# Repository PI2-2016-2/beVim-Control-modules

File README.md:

# beVim-Control-modules
Aplicação baixo nível e módulos de controle do projeto BeVim.
#Histórico

. Pedro Henrique Gonçalves Inazawa - Criação

#Introdução

O sistema BeVim se trata de uma bancada de testes, criada com o intuito de fazer ensaios vibracionais em diversas estruturas. Nesse contexto, dentre os 4 grandes módulos do projeto, o sistema de Controle visa fazer uma "ponte' entre as camadas mais inferiores do projeto (sistema mecânico e de rotação do motor) com as camadas de mais alto nível (sistema web), promovendo interação entre ambos. 

Os objetivos desse grande grupo são:

 * promover o controle transparente das funções de vibração da mesa, ao mesmo tempo que fornecendo dados de como ela está operando. 

 * Ser um sistema modular e escalável também, isto é, deve ser possível aumentar a quantidade de sensores e de motores da mesa da forma que melhor convier para os ensaios feitos na mesa.

 * Promover a vibração correta e com uma estimativa de erro, com um melhor ajuste entre as frequencias de 50 a 100 Hz.

##Módulos básicos do sistema de controle

Três sistemas básicos foram criados: 

 * [Sistema de Sensoriamento](Modules/MeasureBoard/Documentation/MeasureBoard.md): Responsável pela leitura e disponibilização dos dados tanto para os módulos de maior nível dentro do sistema (as CPUs, que se comunicam via UART) quanto por ser MESTRE da comunicação i2c com os módulos logo abaixo.

 * [Sistema de Controle de Motores](Modules/MotorControlBoard/Documentation/MotorControlBoard.md): é um módulo controlado por i2c, que se une a rede criada pelo módulo de sensoriamento. Este é capaz de vibrar os motores, informando os dados pela rede para o módulo de sensoriamento.

 * [Subsistema de expansão de Sensores](Modules/ExpansionBoard/Documentation/ExpansionBoard.md): É um módulo que permite expandir a quantidade de sensores no sistema (de 8 em 8 sensores).

Para mais detalhes sobre esse sistema, consulte a [Arquitetura do Sistema](Documentation/SystemArchitecture.md)

Para mais detalhes sobre os protocolos de comunicação implementados pelo projeto, consulte a [Descrição de protocolos](Simulators/BeVim-Protocol-Simulator/Documentation/Protocol.md)

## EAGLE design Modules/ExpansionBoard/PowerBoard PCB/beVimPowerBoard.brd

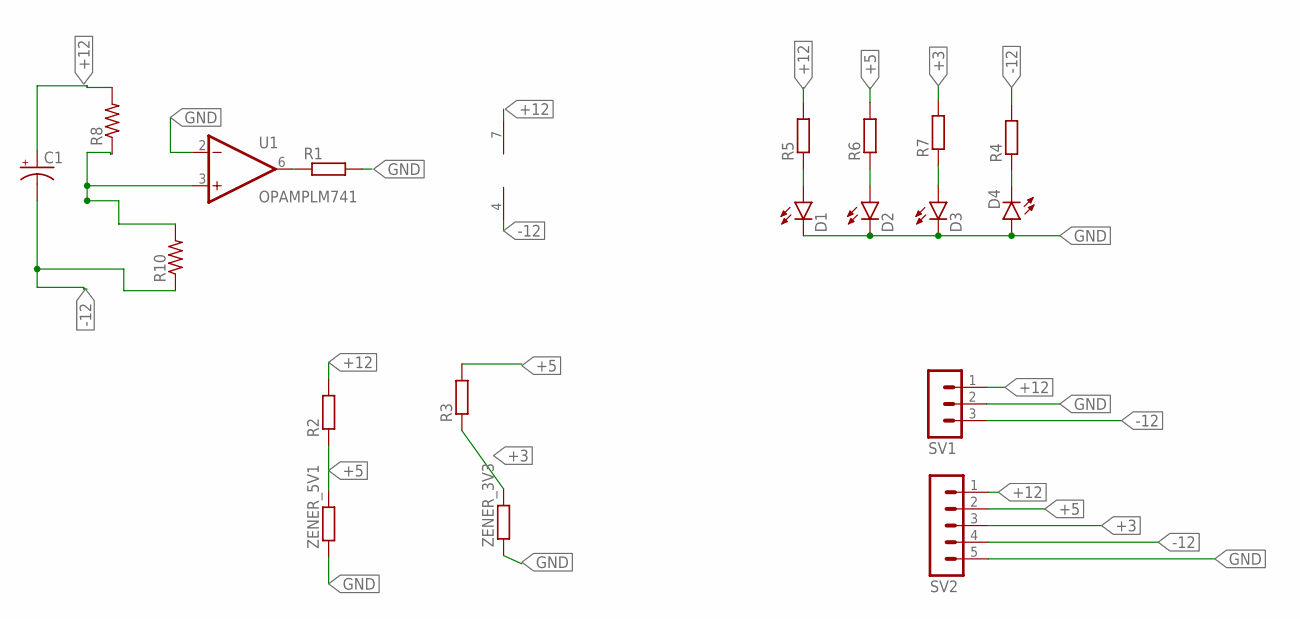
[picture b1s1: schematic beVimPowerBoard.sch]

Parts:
C1: CAPACITOR-POLARIZEDRADIAL-POLARIZED-6.3MM-TANTALUM; RADIAL-POLARIZED-6.3MM-TANTALUM
D1, D2, D3, D4: LED5MM
R1, R2, R3, R4, R5, R6, R7: R-EU_0817/7V; P0817V
R8, R10: R-US_0309/12; 0309/12
SV1: MA03-1
SV2: MA05-1
U1: OPAMPLM741; DIP8
ZENER_3V3, ZENER_5V1: R-EU_0817/7V; P0817V

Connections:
+3: R3.1, R7.2, SV2.3, ZENER_3V3.2
+5: R2.1, R3.2, R6.2, SV2.2, ZENER_5V1.2
+12: C1.+, R2.2, R5.2, R8.2, SV1.1, SV2.1, U1.7 (VCC)
-12: C1.-, R4.2, R10.1, SV1.3, SV2.4, U1.4 (VEE)
GND: D1.K (C), D2.K (C), D3.K (C), D4.A, R1.2, SV1.2, SV2.5, U1.2 (IN-), ZENER_3V3.1, ZENER_5V1.1
unnamed: D1.A, R5.1
unnamed: D2.A, R6.1
unnamed: D3.A, R7.1
unnamed: D4.K (C), R4.1
unnamed: R1.1, U1.6 (OUT)
unnamed: R8.1, R10.2, U1.3 (IN+)

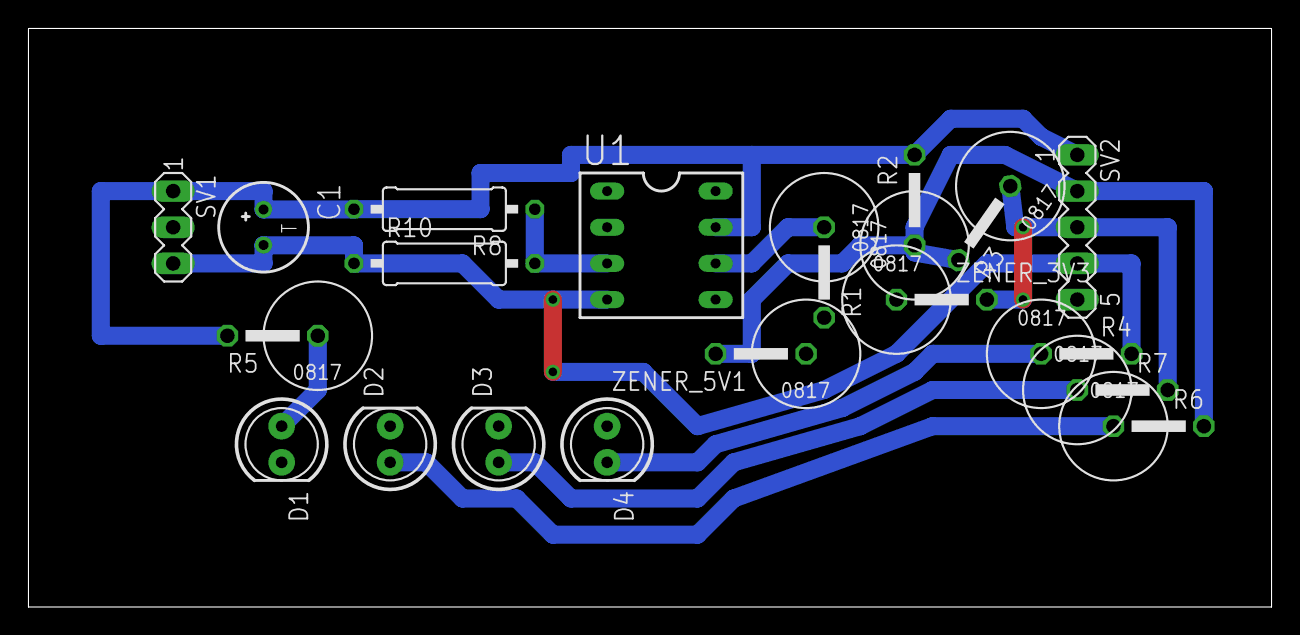
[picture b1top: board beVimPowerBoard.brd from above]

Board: 2 copper layers, 87.3 x 40.6 mm, 19 parts (0 on the bottom side), 11 nets.

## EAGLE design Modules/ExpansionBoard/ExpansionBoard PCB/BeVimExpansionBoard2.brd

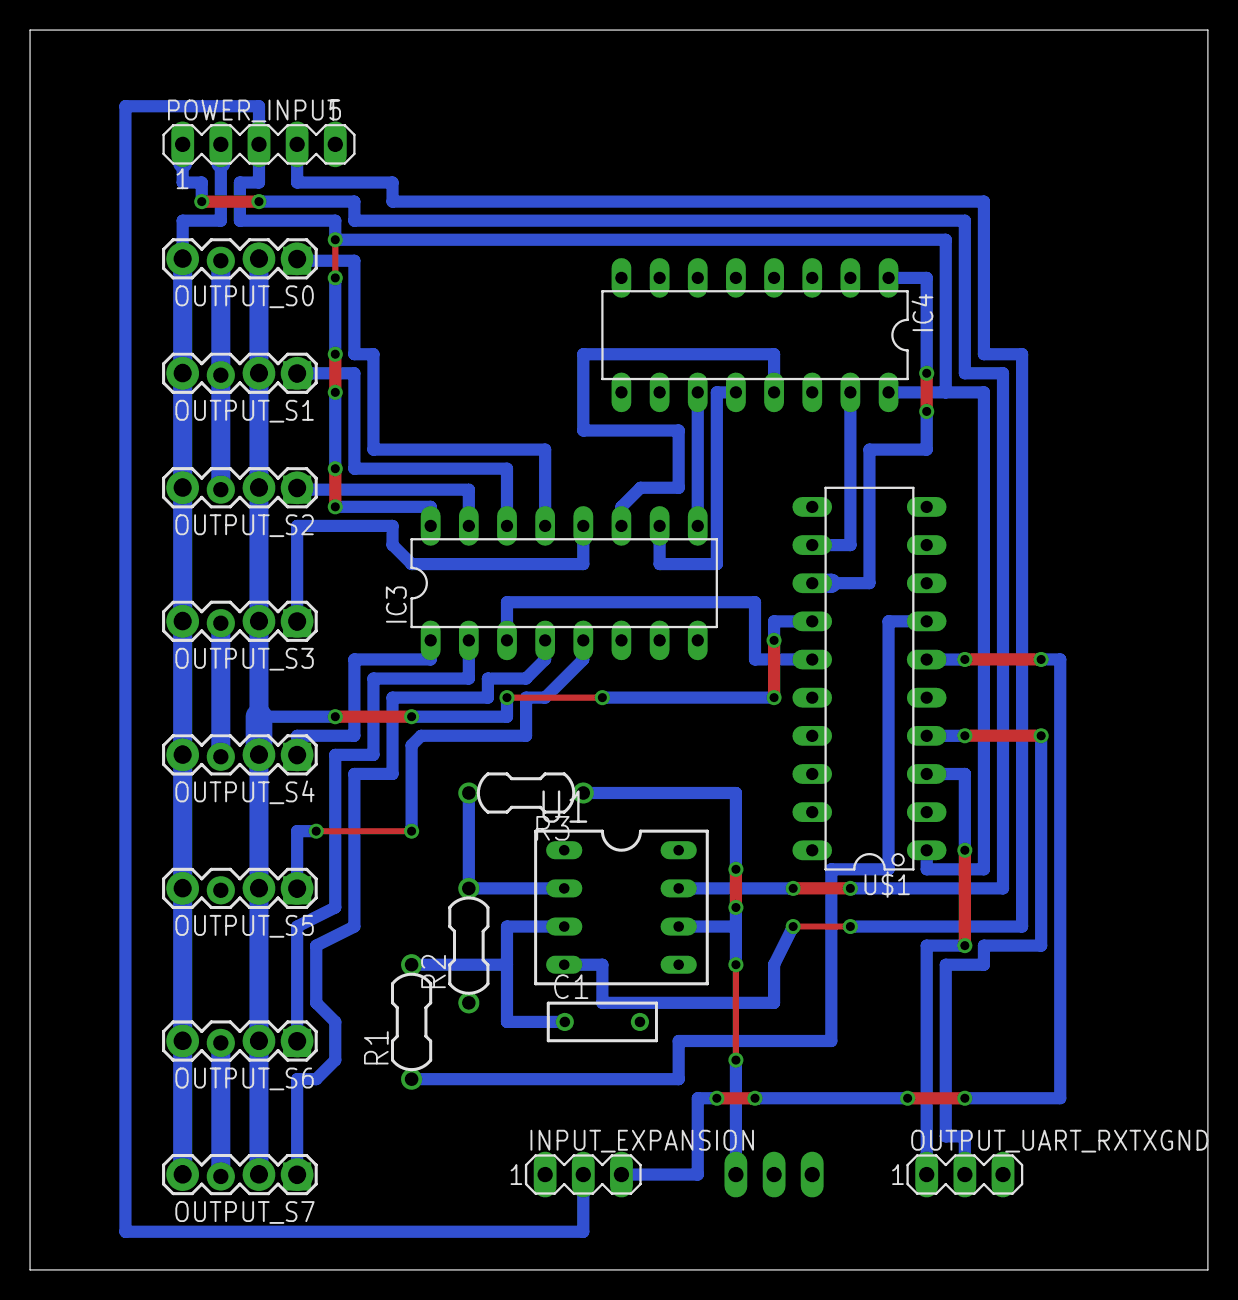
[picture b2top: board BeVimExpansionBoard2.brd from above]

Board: 2 copper layers, 78.4 x 82.5 mm, 20 parts (1 on the bottom side), 27 nets.

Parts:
C1: BOX-2.5MM-7.2MM
IC3: 4051N; DIL16
IC4: 4015N; DIL16
INPUT_EXPANSION: MA03-1
MOTOR_OUTPUT: MA03-1
OUTPUT_S0, OUTPUT_S1, OUTPUT_S2, OUTPUT_S3, OUTPUT_S4, OUTPUT_S5, OUTPUT_S6, OUTPUT_S7: 1X04_LOCK
OUTPUT_UART_RXTXGND: MA03-1
POWER_INPUT: MA05-1
R1, R2, R3: 0.25W-0.3IN
U1: OPAMP; DIP8
U$1: G2X[0/3]2---N20; N20

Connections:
+3: IC3.16, IC4.16, INPUT_EXPANSION.2, POWER_INPUT.3, U$1.1
+5: OUTPUT_S0.4, OUTPUT_S1.4, OUTPUT_S2.4, OUTPUT_S3.4, OUTPUT_S4.4, OUTPUT_S5.4, OUTPUT_S6.4, OUTPUT_S7.4, POWER_INPUT.2
+12: POWER_INPUT.1, U1.7
-12: POWER_INPUT.4, U1.4
CLK: IC4.1, U$1.13
GND: C1.P$2, IC3.6, IC3.7, IC3.8, IC4.8, IC4.14, INPUT_EXPANSION.1, MOTOR_OUTPUT.1, OUTPUT_S0.3, OUTPUT_S1.3, OUTPUT_S2.3, OUTPUT_S3.3, OUTPUT_S4.3, OUTPUT_S5.3, OUTPUT_S6.3, OUTPUT_S7.3, OUTPUT_UART_RXTXGND.3, POWER_INPUT.5, R2.1, U$1.20
INPUT: IC4.15, U$1.12
INPUT_EXP: INPUT_EXPANSION.3, U$1.6
MOTOR: MOTOR_OUTPUT.3, R3.1, U1.6
unnamed: IC3.11, IC4.13
unnamed: IC3.10, IC4.12
unnamed: C1.P$1, R1.2, U1.3
unnamed: R2.2, R3.2, U1.2
unnamed: R1.1, U$1.7
OVRF: IC3.9, IC4.11
RX: OUTPUT_UART_RXTXGND.1, U$1.3
SCL: OUTPUT_S0.2, OUTPUT_S1.2, OUTPUT_S2.2, OUTPUT_S3.2, OUTPUT_S4.2, OUTPUT_S5.2, OUTPUT_S6.2, OUTPUT_S7.2, U$1.14
SDA_MUX: IC3.3, U$1.15
SDA_S0: IC3.13, OUTPUT_S0.1
SDA_S1: IC3.14, OUTPUT_S1.1
SDA_S2: IC3.15, OUTPUT_S2.1
SDA_S3: IC3.12, OUTPUT_S3.1
SDA_S4: IC3.1, OUTPUT_S4.1
SDA_S5: IC3.5, OUTPUT_S5.1
SDA_S6: IC3.2, OUTPUT_S6.1
SDA_S7: IC3.4, OUTPUT_S7.1
TX: OUTPUT_UART_RXTXGND.2, U$1.4

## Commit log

2016-09-22 Atualização da documentação
    Descrição inicial do protocolo.
2016-09-24 Adição de unidades aos eixos e a timestamp do gráfico
2016-09-25 Adição de simulador Mudança dos arquivos que descrevem a arquitetura.
2016-09-26 Estrutura de Pastas + Esquemático da placa de extensão
    -Criação de estruturas de pastas para acomodar melhor os projetos a
    serem desenvolvidos.
    - Criação de esquemático inicial para o sistema de expansão de portas de
    i2c.
2016-09-26 Correção de texto de Markdown
    Correção das links simbólicas dentro do texto
    Correção de tópicos.
2016-09-26 Adaptação de markdown
2016-09-26 Correção de nome do arquivo
2016-09-26 Correção de nome de arquivo
2016-09-26 Correção de Markdown
2016-09-26 Arquivo Duplicado
2016-09-26 Atualização de Markdown
2016-09-26 Mudança de Markdown,
    Adição de link para os protocolos na página inicial.
2016-09-26 Correção do nome do md
2016-09-28 Adição de camada BSP GPIO ao desenvolvimento. Criação de estrutura do BSP
2016-10-01 COrreção dos módulos de GPIOs - Adição de breaks que estavam faltando na função de mudança de output.
    Correção do exemplo - Inclusão de teste via botão
2016-10-07 Modificando o simulador para exibir mensagens de debug apenas se a flag __verbose estiver ativa.
2016-10-07 Mudanças no programa que implementa o protocolo para eliminar a impressão da frequencia fora do modo verbose.
2016-10-08 Inclusão de arquivos de documentação do projeto (dos MSP430 utilizados)
    Inclusão de nova biblioteca do BSP - clock-Manager (implementação apenas para o f2274 até o momento.
    Modificação do exemplo de uart para inserir interface de clock criada.
2016-10-21 Adding adjustments in sensor data
2016-10-21 Corrigindo função de clock, e de uart. Subindo exemplo
2016-10-23 Adição de script para programação automatica e modificação do makefile para ser utilizar o script com a diretiva install. Melhorias no código exemplo de UART, e atualização para a ultima interface de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
2016-10-23 Ajustes no exemplo de uso da uart para ultima versão da interface.
2016-10-24 Adequação da biblioteca de uart e retirada de bugs relativos a condições de corrida entre interrupção e pooling durante o recebimento de bytes.
    Adequação do exemplo de uart a ultima interface da biblioteca. Observar que há limitações no uso de pooling ao se utilizar interrupçoes, então o ideal é nunca utilizar as duas formas juntas (meu pens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
2016-10-25 Adding adjustments in arduino simulator program
2016-10-25 Modificação no Makefile para que apague os .o gerados durante o processo de compilação da lib.
2016-11-02 Documentacao e esquematicos para placa de expansao
2016-11-02 Esquematicos dac/controle inversor
2016-11-05 itens relatorio
2016-11-05 atualizando figuras
2016-11-05 detalhamento
2016-11-10 Formalização protocolo BEViM
2016-11-14 Melhoria do Protocolo
2016-11-16 Adição de suporte a i2c. Adição de biblioteca de interface com MPU60x0. Adição de exemplo de comunicação com MPU60x0.
2016-11-19 Inclusão de PCBs de placa de controle e de placa de fontes.
    Foi feito na versão do eagle 7.3.0 Light
2016-11-20 Atualização da placa de controle para ter entrada para a placa de expansao
2016-11-28 Inclusao de biblioteca de timerA + Example
    Inclusão na biblioteca de timer A de ponteiro de função para interrupção
2016-11-28 Inclusão da primeira versão da aplicação da mesa
2016-11-30 Inclusão de biblioteca para leitura em frequencia,
    correçoes na aplicação do MCU para que o controle via interrupção seja efetuado
2016-12-04 ultima versao para usar no PC do paulo
2016-12-08 inclusão de interrupção mais genérica
2016-12-08 Inclusão de limiares de frequencia requerida e calculo de frequencia
    Inclui o novo calculo da frequencia.
    Cria limiares compilados no código para frequencia da mesa, e frequencia
    requerida.
2016-12-11 Commit final
    Atualização da ultima versão do projeto

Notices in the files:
parts and their libraries:
SparkFun-Connectors: Licensing: Creative Commons ShareAlike 4.0 International - https://creativecommons.org/licenses/by-sa/4.0
